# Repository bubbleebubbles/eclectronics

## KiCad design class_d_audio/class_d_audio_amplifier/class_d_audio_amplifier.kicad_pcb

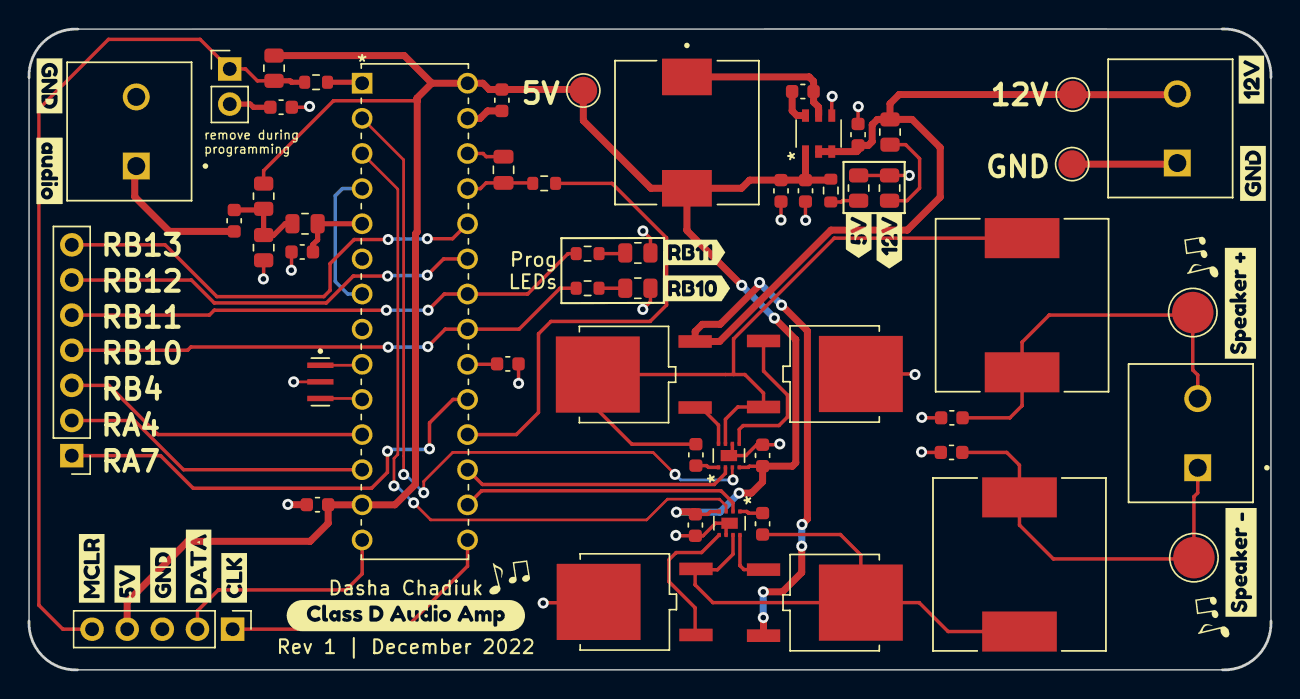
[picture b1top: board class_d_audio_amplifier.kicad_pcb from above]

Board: 2 copper layers, 89.8 x 46.3 mm, 70 parts (0 on the bottom side), 42 nets.

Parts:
C1, C13: 1uF; C_0603_1608Metric
C2, C14: 10uF; C_0603_1608Metric
C3, C4, C10, C12, C15, C17: .1uF; C_0603_1608Metric
C5, C6: 22uF; C_0603_1608Metric
C7, C8: 2.2uF; C_0603_1608Metric
C9: .082uF; C_0603_1608Metric
C11: 820pF; C_0603_1608Metric
C16: 5000pF; C_0805_2012Metric
D1, D2, D3, D4: LED_BLUE; R_0805_2012Metric
J1, J2, J5: Conn_01x02; CUI_TB001-500-02BE
J3: Conn_01x07; PinHeader_1x07_P2.54mm_Vertical
J4: Conn_01x05; PinHeader_1x05_P2.54mm_Vertical
JP1: Jumper; PinHeader_1x02_P2.54mm_Vertical
L1: 3.9uH; IND_B966AS
L2, L3: 27uH; INDP125125X600N
Q1, Q2, Q3, Q4: MCU80N03A-TP
R1: 1k; R_0805_2012Metric
R2, R6, R7, R9, R10: 200; R_0603_1608Metric
R3, R4, R5, R8: 10k; R_0805_2012Metric
TP1, TP2, TP3: TP; TestPoint_Pad_D2.0mm
TP4: Speaker_Out1; TestPoint_Pad_D3.0mm
TP5: Speaker_Out2; TestPoint_Pad_D3.0mm
U1, U3: NCP81151MNTBG
U2: AP63205WU-7; AP63203WU-7
U4: PIC24FV16KM202
Y1: 8MHz_Crystal; OSC_CSTNE8M00G550000R0
kibuzzard-638C4FD3, kibuzzard-638C4FD3#2: G***; kibuzzard-638C4FD3
kibuzzard-638C50B6: G***; kibuzzard-638C50B6
kibuzzard-638C52FC: G***; kibuzzard-638C52FC
kibuzzard-638C54CC: G***; kibuzzard-638C54CC
kibuzzard-638C55E5: G***; kibuzzard-638C55E5
kibuzzard-638C55ED: G***; kibuzzard-638C55ED
kibuzzard-638C57B8: G***; kibuzzard-638C57B8
kibuzzard-638C507C: G***; kibuzzard-638C507C
kibuzzard-638C509A: G***; kibuzzard-638C509A
kibuzzard-638C516B: G***; kibuzzard-638C516B
kibuzzard-638C543F: G***; kibuzzard-638C543F
kibuzzard-638C5059: G***; kibuzzard-638C5059
kibuzzard-638C5180: G***; kibuzzard-638C5180
kibuzzard-638C5303: G***; kibuzzard-638C5303
kibuzzard-638C5384: G***; kibuzzard-638C5384

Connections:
+5V: C1.1, C5.1, C6.1, C12.1, C13.1, C15.1, J4.4, L1.2, R2.1, R3.1, R8.1, TP2.1 (TP), U1.4 (VCC), U2.1 (FB), U3.4 (VCC), U4.13 (VDD), U4.28 (AVDD)
+12V: C2.1, J1.2, Q1.2, Q3.2, R1.1, TP3.1 (TP), U2.2 (EN), U2.3 (VIN)
/DR_EN_H: U1.3 (EN), U4.2 (RA0)
/DR_EN_L: U3.3 (EN), U4.3 (RA1)
/ICSP_CLK: J4.1, U4.15 (RB6)
/ICSP_DATA: J4.2, U4.14 (RB5)
/PWM_H: U1.2 (PWM), U4.17 (RB8)
/PWM_L: U3.2 (PWM), U4.16 (RB7)
/RA4: J3.2, U4.12 (RA4)
/RA7: J3.1, U4.19 (RA7)
/RB4: J3.3, U4.11 (RB4)
/RB10: J3.4, R10.1, U4.21 (RB10)
/RB11: J3.5, R9.1, U4.22 (RB11)
/RB12: J3.6, U4.23 (RB12)
/RB13: J3.7, U4.24 (RB13)
/audio_buffered_in: U4.4 (RB0), U4.7 (RB3)
/audio_filtered: C11.1, R5.2, U4.5 (RB1)
/audio_in: C9.1, J5.1
/speaker+: C7.1, J2.2, L2.2, TP4.1 (TP)
/speaker-: C8.1, J2.1, L3.1, TP5.1 (TP)
/triangle_wave_out: C16.1, U4.26 (RB15)
/~MCLR: J4.5, JP1.1 (A), R7.2, R8.2
GND: C1.2, C2.2, C5.2, C6.2, C7.2, C8.2, C11.2, C12.2, C13.2, C14.2, C15.2, C17.2, D1.1, D2.1, D3.1, D4.1, J1.1, J4.3, J5.2, Q2.3, Q4.3, R4.2, TP1.1 (TP), U2.4 (GND), U3.6 (GND), U3.9 (FLAG), U4.8 (VSS), U4.27 (AVSS), Y1.2
unnamed: C3.2, L2.1, Q1.3, Q2.2
unnamed: C4.1, U2.6 (BST)
unnamed: C4.2, L1.1, U2.5 (SW)
unnamed: C9.2, R3.2, R4.1, R5.1
unnamed: C10.1, U3.1 (BST)
unnamed: C10.2, L3.2, Q3.3, Q4.2, U3.7 (SW)
unnamed: C14.1, U4.20 (RA6/VDDCORE)
unnamed: C16.2, R6.2, U4.25 (RB14)
unnamed: C17.1, JP1.2 (B)
unnamed: D1.2, R1.2
unnamed: D2.2, R2.2
unnamed: D3.2, R9.2
unnamed: D4.2, R10.2
unnamed: Q3.1, U3.8 (DRVH)
unnamed: Q4.1, U3.5 (DRVL)
unnamed: R6.1, U4.18 (RB9)
unnamed: R7.1, U4.1 (*MCLR/RA5)
unnamed: U4.9 (RA2), Y1.1
unnamed: U4.10 (RA3), Y1.3

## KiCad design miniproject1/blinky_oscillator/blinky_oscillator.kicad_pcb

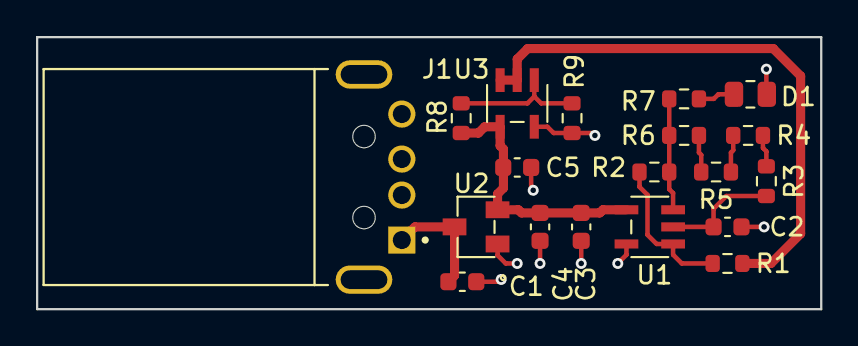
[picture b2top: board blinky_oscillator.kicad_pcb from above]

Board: 2 copper layers, 43.6 x 15.1 mm, 19 parts (0 on the bottom side), 12 nets.

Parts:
C1, C4: C_1uF; C_0603_1608Metric
C2: C_10000pF; C_0603_1608Metric
C3, C5: C_0.1uF; C_0603_1608Metric
D1: LED_BLUE; R_0805_2012Metric
J1: USB2_A; MOLEX_48037-0001
R1: R_1.58k; R_0603_1608Metric
R2: R_301; R_0603_1608Metric
R3, R4: R_10M; R_0603_1608Metric
R5: R_402k; R_0603_1608Metric
R6: R_69.8k; R_0603_1608Metric
R7: R_31.6; R_0603_1608Metric
R8, R9: R_1k; R_0603_1608Metric
U1, U3: MCP6021T-EOT; MCP6021T-E_OT
U2: MCP1702T-3302ECB; MCP1702T-3302E&slash_CB

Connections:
+3.3V: C3.1, C4.1, C5.1, R8.1, U1.4 (V+), U2.2 (VOUT), U3.4 (V+)
+5V: C1.1, J1.1 (VBUS), U2.3 (VIN)
/Vref: R8.2, R9.1, U3.1 (+)
/Vref_Buffered: R1.1, U3.2 (-), U3.3
GND: C1.2, C2.2, C3.2, C4.2, C5.2, D1.1, J1.4 (GND), R9.2, U1.5 (V-), U2.1 (GND), U3.5 (V-)
unnamed: C2.1, R3.1, U1.2 (-)
unnamed: D1.2, R7.2
unnamed: R1.2, R2.2, U1.1 (+)
unnamed: R3.2, R4.1
unnamed: R4.2, R5.1
unnamed: R5.2, R6.1
unnamed: R2.1, R6.2, R7.1, U1.3

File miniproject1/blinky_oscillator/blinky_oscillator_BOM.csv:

"Id";"Designator";"Package";"Quantity";"Designation";"Supplier and ref";
1;"R1";"R_0603_1608Metric";1;"R_1.58k";;;
2;"J1";"MOLEX_48037-0001";1;"USB2_A";;;
3;"R2";"R_0603_1608Metric";1;"R_301";;;
4;"C2";"C_0603_1608Metric";1;"C_10000pF";;;
5;"C3,C5";"C_0603_1608Metric";2;"C_0.1uF";;;
6;"R3,R4";"R_0603_1608Metric";2;"R_10M";;;
7;"U2";"MCP1702T-3302E&slash_CB";1;"MCP1702T-3302ECB";;;
8;"R7";"R_0603_1608Metric";1;"R_31.6";;;
9;"R9,R8";"R_0603_1608Metric";2;"R_1k";;;
10;"C1,C4";"C_0603_1608Metric";2;"C_1uF";;;
11;"U1,U3";"MCP6021T-E_OT";2;"MCP6021T-EOT";;;
12;"R6";"R_0603_1608Metric";1;"R_69.8k";;;
13;"R5";"R_0603_1608Metric";1;"R_402k";;;
14;"D1";"R_0805_2012Metric";1;"LED_BLUE";;;

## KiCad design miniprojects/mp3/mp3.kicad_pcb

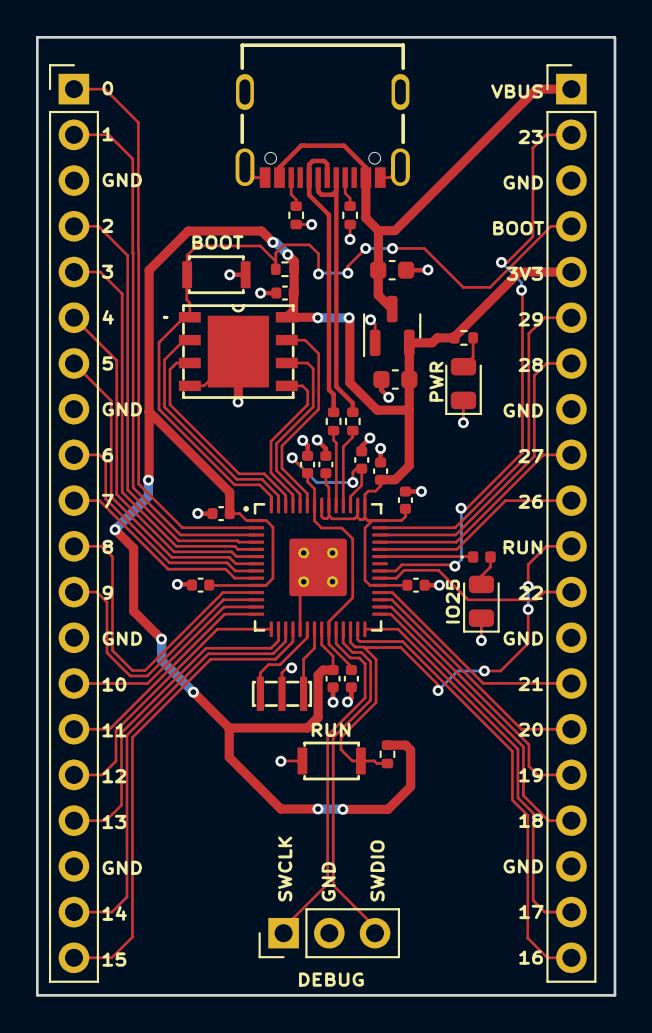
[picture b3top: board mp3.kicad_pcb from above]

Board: 2 copper layers, 32.1 x 53.2 mm, 33 parts (0 on the bottom side), 52 nets.

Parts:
C1, C2, C3, C4, C5, C6, C7, C10, C11: 0.1µF; C_0402_1005Metric
C8, C9: 1µF; C_0402_1005Metric
C12, C13: 10µF; C_0603_1608Metric
D1: LED; LED_0805_2012Metric
D2: PWR; LED_0805_2012Metric
J1: USB4105-GF-A
J2: LEFT; PinHeader_1x20_P2.54mm_Vertical
J3: DEBUG; PinHeader_1x03_P2.54mm_Vertical
J4: RIGHT; PinHeader_1x20_P2.54mm_Vertical
R1, R2, R3, R4: 5.1K; R_0402_1005Metric
R5, R6: 27Ω; R_0402_1005Metric
R7: 1K; LED_0402_1005Metric
R8: 1K; R_0402_1005Metric
S1: RST; KXT321LHS
S2: BOOT; KXT321LHS
U1: W25Q128JV; MIC_WSON-8-M
U2: RP2040
U3: MCP1702T-3302E_CB; SOT-23
Y1: 12MHz; CSTNE

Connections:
+3V3: C1.2, C2.1, C3.1, C4.1, C5.1, C6.1, C7.1, C8.1, C13.1, J4.5, R2.2, R3.2, R8.1, U1.8 (VDD), U2.1 (IOVDD), U2.10 (IOVDD), U2.22 (IOVDD), U2.33 (IOVDD), U2.42 (IOVDD), U2.43 (ADC_AVDD), U2.44 (VREG_VIN), U2.48 (USB_VDD), U2.49 (IOVDD), U3.2 (VOUT)
/BOOT: J4.4, R3.1, S2.2, U1.1 (~CS), U2.56 (~QSPI_CS)
/GPIO0: J2.1, U2.2 (GPIO0)
/GPIO1: J2.2, U2.3 (GPIO1)
/GPIO2: J2.4, U2.4 (GPIO2)
/GPIO3: J2.5, U2.5 (GPIO3)
/GPIO4: J2.6, U2.6 (GPIO4)
/GPIO5: J2.7, U2.7 (GPIO5)
/GPIO6: J2.9, U2.8 (GPIO6)
/GPIO7: J2.10, U2.9 (GPIO7)
/GPIO8: J2.11, U2.11 (GPIO8)
/GPIO9: J2.12, U2.12 (GPIO9)
/GPIO10: J2.14, U2.13 (GPIO10)
/GPIO11: J2.15, U2.14 (GPIO11)
/GPIO12: J2.16, U2.15 (GPIO12)
/GPIO13: J2.17, U2.16 (GPIO13)
/GPIO14: J2.19, U2.17 (GPIO14)
/GPIO15: J2.20, U2.18 (GPIO15)
/GPIO16: J4.20, U2.27 (GPIO16)
/GPIO17: J4.19, U2.28 (GPIO17)
/GPIO18: J4.17, U2.29 (GPIO18)
/GPIO19: J4.16, U2.30 (GPIO19)
/GPIO20: J4.15, U2.31 (GPIO20)
/GPIO21: J4.14, U2.32 (GPIO21)
/GPIO22: J4.12, U2.34 (GPIO22)
/GPIO23: J4.2, U2.35 (GPIO23)
/GPIO25: R7.1, U2.37 (GPIO25)
/GPIO26: J4.10, U2.38 (GPIO26/ADC0)
/GPIO27: J4.9, U2.39 (GPIO27/ADC1)
/GPIO28: J4.7, U2.40 (GPIO28/ADC2)
/GPIO29: J4.6, U2.41 (GPIO29/ADC3)
/RUN: J4.11, R2.1, S1.2, U2.26 (RUN)
/SWCLK: J3.1, U2.24 (SWCLK)
/SWDIO: J3.3, U2.25 (SWDIO)
/VBUS: C12.2, J1.A4B9 (VBUS), J1.B4A9 (VBUS), J4.1, U3.3 (VIN)
GND: C1.1, C2.2, C3.2, C4.2, C5.2, C6.2, C7.2, C8.2, C9.2, C10.2, C11.2, C12.1, C13.2, D1.1 (K), D2.1 (K), J1.A1B12 (GND), J1.B1A12 (GND), J1.S1 (SHELL), J1.S2 (SHELL), J1.S3 (SHELL), J1.S4 (SHELL), J2.3, J2.8, J2.13, J2.18, J3.2, J4.3, J4.8, J4.13, J4.18, R1.2, R4.2, S1.1, S2.1, U1.4 (GND), U1.9 (EP), U2.19 (TESTEN), U2.57 (GND), U3.1 (GND), Y1.2
unnamed: C9.1, C10.1, C11.1, U2.23 (DVDD), U2.45 (VREG_VOUT), U2.50 (DVDD)
unnamed: D1.2 (A), R7.2
unnamed: D2.2 (A), R8.2
unnamed: J1.A5 (CC1), R4.1
unnamed: J1.A6 (D+), J1.B6 (D+), R6.1
unnamed: J1.A7 (D-), J1.B7 (D-), R5.1
unnamed: J1.B5 (CC2), R1.1
unnamed: R5.2, U2.46 (USB_D-)
unnamed: R6.2, U2.47 (USB_D+)
unnamed: U1.2 (DO/IO1), U2.55 (QSPI_SD1)
unnamed: U1.3 (~WP/IO2), U2.54 (QSPI_SD2)
unnamed: U1.5 (DI/IO0), U2.53 (QSPI_SD0)
unnamed: U1.6 (SCK), U2.52 (QSPI_SCLK)
unnamed: U1.7 (~HOLD/IO3), U2.51 (QSPI_SD3)
unnamed: U2.20 (XIN), Y1.1
unnamed: U2.21 (XOUT), Y1.3

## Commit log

2022-09-16 added schematic and layout for miniproject 1
2022-09-16 added symbol and footprint libraries
2022-09-16 exported schematic pdf
2022-09-16 added images of pcb
2022-09-16 added miniproject1 ltspice files
2022-09-16 added MATLAB tolerance analysis script
2022-09-16 Added simulation data
    includes zipfile that has text data from the simulations run in LTspice
2022-09-16 added supporting MATLAB files for miniproject 1
    added loadspice.m which loads LTspice text data
    added period.mat and data.mat that contains the most recent collected data
2022-09-16 added pdf of the miniproject1 writeup
2022-09-16 moved all MATLAB files into MATLAB folder
2022-09-16 added MATLAB_oscillator folder with MATLAB files
2022-09-16 added BOM
2022-09-28 added mp3 project files and libraries
2022-10-12 completed mp3 layout
2022-10-12 refilled zones
2022-10-12 fixed bypass cap gnd traces
2022-10-12 fixed DRC errors -- uploaded final layout
2022-12-02 schematic and parts added
2022-12-02 removed unused files
2022-12-02 added pdf of schematic
2022-12-02 correction to quality factor note on LC filter
2022-12-04 completed layout
2022-12-06 modified parts library and exported bom
2022-12-06 created hardware, firmware folders and moved files into respective folders
2022-12-10 moved miniprojects files into miniprojects folder
2022-12-10 Added pre-commit config file
    Runs selected pre-commit checks at each commit to format and clean
    up files.
2022-12-10 removed unnecessary folders since all projects were moved to miniprojects folder

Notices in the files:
parts and their libraries:
Copyright 2021 Accelerated Designs. All rights reserved.
